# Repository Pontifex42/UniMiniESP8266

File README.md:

# UniMiniESP8266

For common simple microcontroller applications, I created a very tiny board in the size of an 18650 cell.
In many cases, the 3,0V - 4,2V of a single cell is sufficient, which makes it extremely simple to build working circuits.
There are many pins for power supply, so there is no more breadbord wiring or perfboard wiring hell.

What it can do for you:
- easyly powered with a single 18650 lithium cell, works down to 3,2V discharge due to LDO
- drives up to 6 servos (using 18650 voltage)
- has two pins with transitor-outputs, if populated
- can have an H-bridge using L9110
- onboard switch intended (or use a solder bridge)
- WiFi ability due to the power of ESP8266

To download code, use a FTDI-adapter, shorten pin M1 to ground and press reset or, if reset switch is not populated, just power on.

As an example, have a look in my "Servo-Tester" repository on github:
https://github.com/Pontifex42/ServoTester

It uses ESP8266-12F module, I will create an improved version using ESP-C3-12F soon.

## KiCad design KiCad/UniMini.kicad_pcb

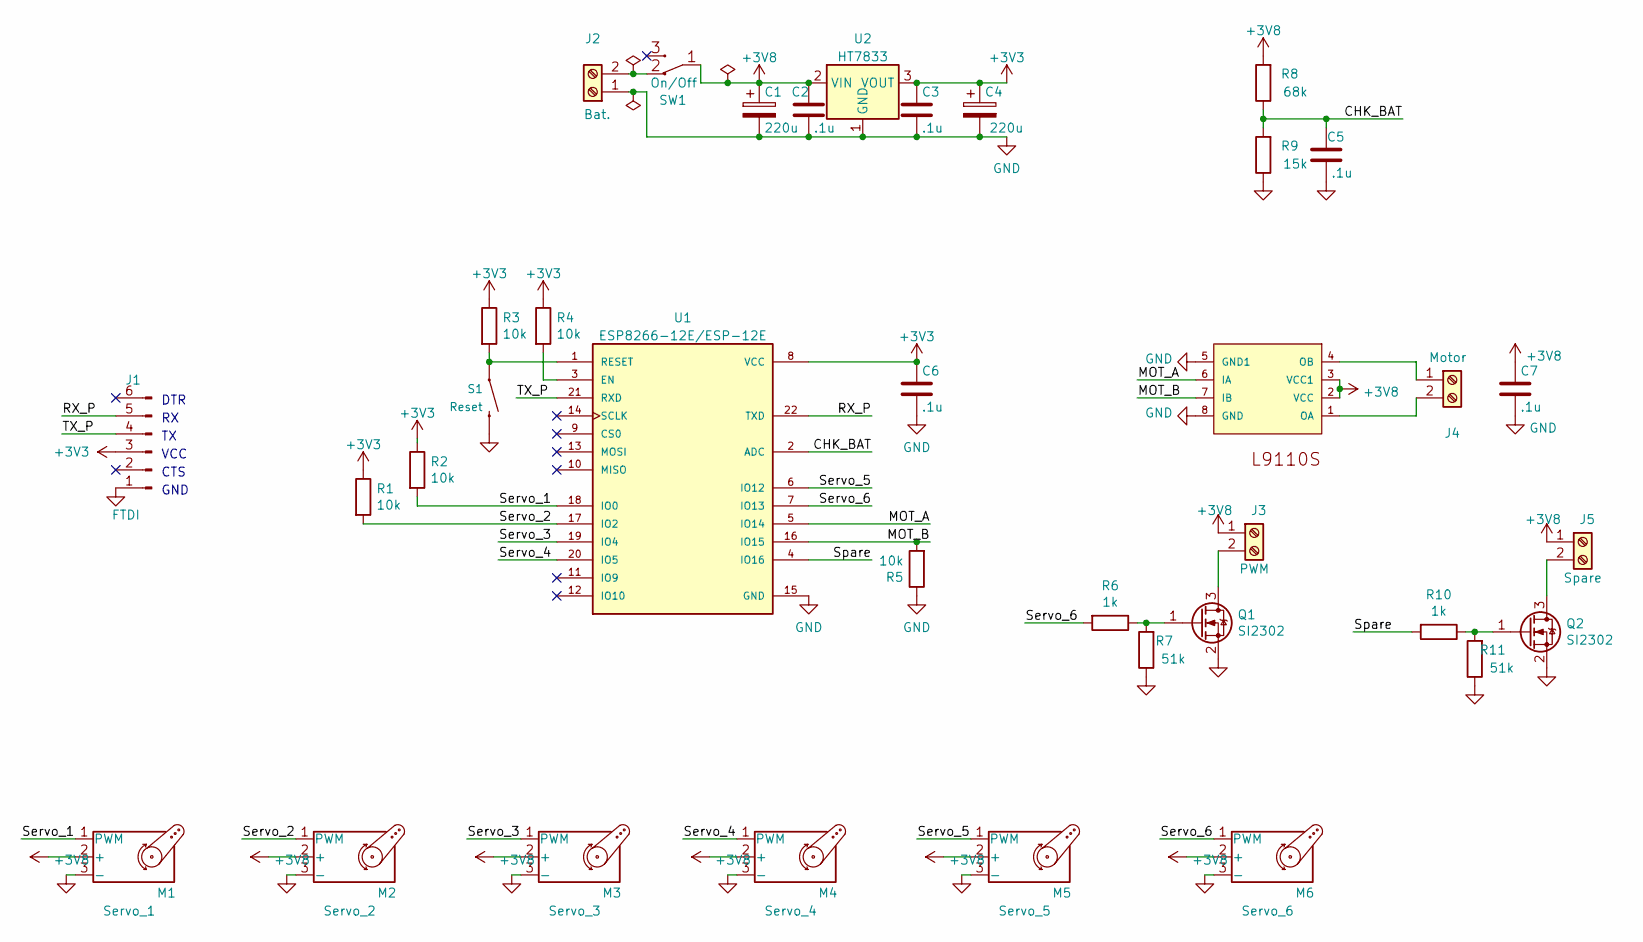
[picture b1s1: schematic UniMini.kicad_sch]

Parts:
C1, C4: 220u; CP_Elec_8x10.5
C2, C3, C5, C6, C7: .1u; C_0805_2012Metric_Pad1.18x1.45mm_HandSolder
J1: FTDI; PinHeader_1x06_P2.54mm_Vertical
J2: Bat.; PinHeader_1x02_P2.54mm_Vertical
J3: PWM; PinHeader_1x02_P2.54mm_Vertical
J4: Motor; PinHeader_1x02_P2.54mm_Vertical
J5: Spare; PinHeader_1x02_P2.54mm_Vertical
M1: Servo_1; PinHeader_1x03_P2.54mm_Vertical
M2: Servo_2; PinHeader_1x03_P2.54mm_Vertical
M3: Servo_3; PinHeader_1x03_P2.54mm_Vertical
M4: Servo_4; PinHeader_1x03_P2.54mm_Vertical
M5: Servo_5; PinHeader_1x03_P2.54mm_Vertical
M6: Servo_6; PinHeader_1x03_P2.54mm_Vertical
Q1, Q2: SI2302; SOT-23
R1, R2, R3, R4, R5: 10k; R_0805_2012Metric_Pad1.20x1.40mm_HandSolder
R6, R10: 1k; R_0805_2012Metric_Pad1.20x1.40mm_HandSolder
R7, R11: 51k; R_0805_2012Metric_Pad1.20x1.40mm_HandSolder
R8: 68k; R_0805_2012Metric_Pad1.20x1.40mm_HandSolder
R9: 15k; R_0805_2012Metric_Pad1.20x1.40mm_HandSolder
S1: Reset; TACTILE_SWITCH_SMD_6.0X3.5MM
SW1: On/Off; MST-22D01_Standing
U1: ESP8266-12E/ESP-12E; XCVR_ESP8266-12E_ESP-12E
U2: HT7833; SOT-89-3
U3: L9110S; SOIC127P600X150-8

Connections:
+3V3: C3.1, C4.1, C6.1, J1.3, R1.1, R2.1, R3.1, R4.1, U1.8 (VCC), U2.3 (VOUT)
+3V8: C1.1, C2.1, C7.1, J3.1, J5.1, M1.2 (+), M2.2 (+), M3.2 (+), M4.2 (+), M5.2 (+), M6.2 (+), R8.2, SW1.1 (COM), U2.2 (VIN), U3.2 (VCC), U3.3 (VCC1)
/CHK_BAT: C5.1, R8.1, R9.2, U1.2 (ADC)
/MOT_A: U1.5 (IO14), U3.6 (IA)
/MOT_B: R5.2, U1.16 (IO15), U3.7 (IB)
/RX_P: J1.5, U1.22 (TXD)
/Servo_1: M1.1 (PWM), R2.2, U1.18 (IO0)
/Servo_2: M2.1 (PWM), R1.2, U1.17 (IO2)
/Servo_3: M3.1 (PWM), U1.19 (IO4)
/Servo_4: M4.1 (PWM), U1.20 (IO5)
/Servo_5: M5.1 (PWM), U1.6 (IO12)
/Servo_6: M6.1 (PWM), R6.2, U1.7 (IO13)
/Spare: R10.2, U1.4 (IO16)
/TX_P: J1.4, U1.21 (RXD)
GND: C1.2, C2.2, C3.2, C4.2, C5.2, C6.2, C7.2, J1.1, J2.1, M1.3 (-), M2.3 (-), M3.3 (-), M4.3 (-), M5.3 (-), M6.3 (-), Q1.2 (S), Q2.2 (S), R5.1, R7.1, R9.1, R11.1, S1.2, U1.15 (GND), U2.1 (GND), U3.5 (GND1), U3.8 (GND)
unnamed: J2.2, SW1.2 (NC)
unnamed: J3.2, Q1.3 (D)
unnamed: J4.1, U3.4 (OB)
unnamed: J4.2, U3.1 (OA)
unnamed: J5.2, Q2.3 (D)
unnamed: Q1.1 (G), R6.1, R7.2
unnamed: Q2.1 (G), R10.1, R11.2
unnamed: R3.2, S1.1, U1.1 (RESET)
unnamed: R4.2, U1.3 (EN)

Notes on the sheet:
DTR
VCC
CTS
GND

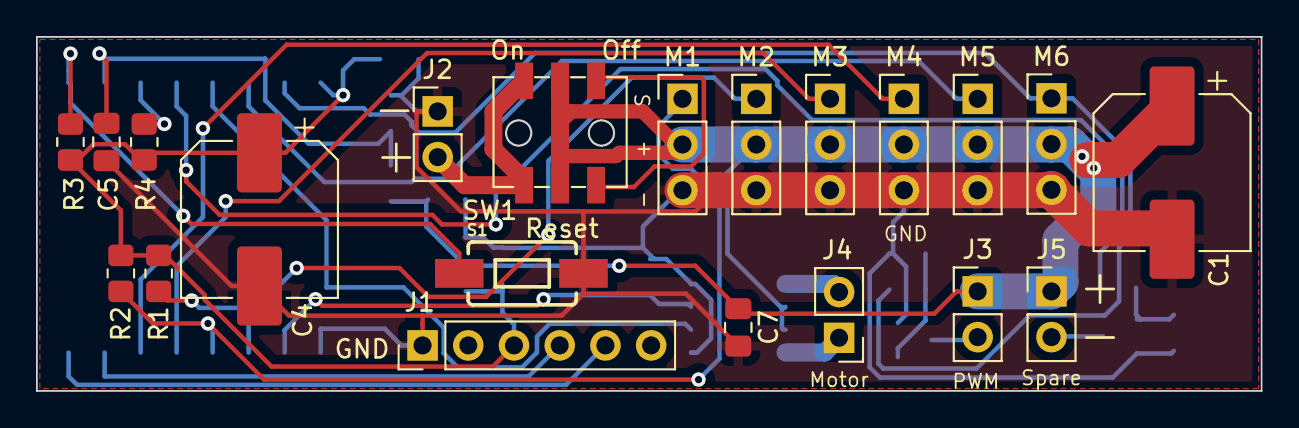
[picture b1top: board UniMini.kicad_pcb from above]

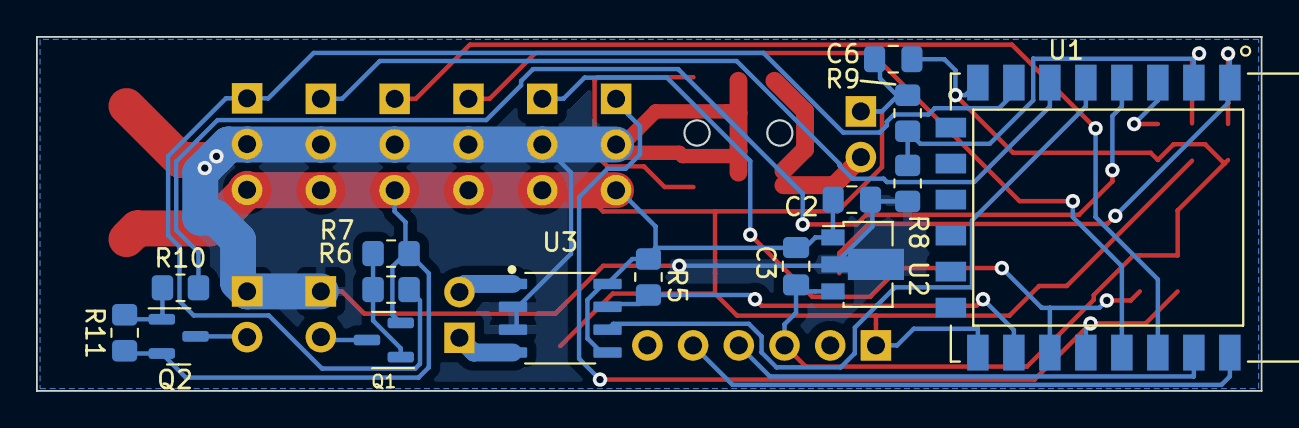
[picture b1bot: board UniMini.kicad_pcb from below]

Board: 2 copper layers, 68.0 x 19.6 mm, 36 parts (15 on the bottom side), 24 nets.

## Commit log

2022-10-27 Version 2 working great
